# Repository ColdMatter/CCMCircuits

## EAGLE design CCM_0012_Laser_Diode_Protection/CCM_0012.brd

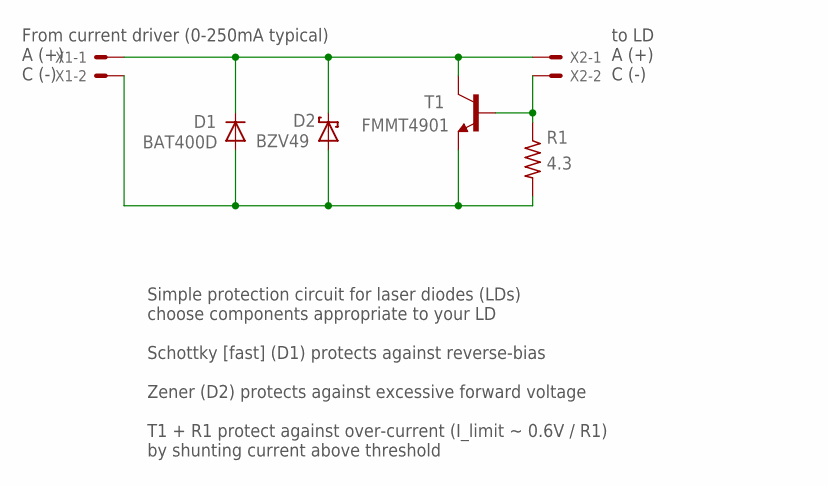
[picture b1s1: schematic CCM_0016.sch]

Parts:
D1: BAT400D; SOT23
D2: BZV49; SOT89
R1: 4.3; 2512
T1: FMMT4901; SOT23-BEC
X1, X2: 22-23-2021

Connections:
unnamed: R1.1, T1.B, X2.2
unnamed: D1.1 (A), D2.1 (A), D2.3 (A), R1.2, T1.E, X1.2
unnamed: D1.3 (C), D2.2 (C), D2.2@1 (C), T1.C, X1.1, X2.1

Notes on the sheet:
From current driver (0-250mA typical) A (+) C (-)
to LD A (+) C (-)
Simple protection circuit for laser diodes (LDs) choose components appropriate to your LD Schottky [fast] (D1) protects against reverse-bias Zener (D2) protects against excessive forward voltage T1 + R1 protect against over-current (I_limit ~ 0.6V / R1) by shunting current above threshold

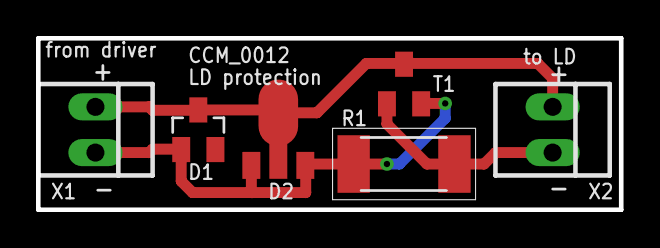
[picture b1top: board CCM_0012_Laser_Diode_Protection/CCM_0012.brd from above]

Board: 2 copper layers, 32.4 x 9.5 mm, 6 parts (0 on the bottom side), 3 nets.

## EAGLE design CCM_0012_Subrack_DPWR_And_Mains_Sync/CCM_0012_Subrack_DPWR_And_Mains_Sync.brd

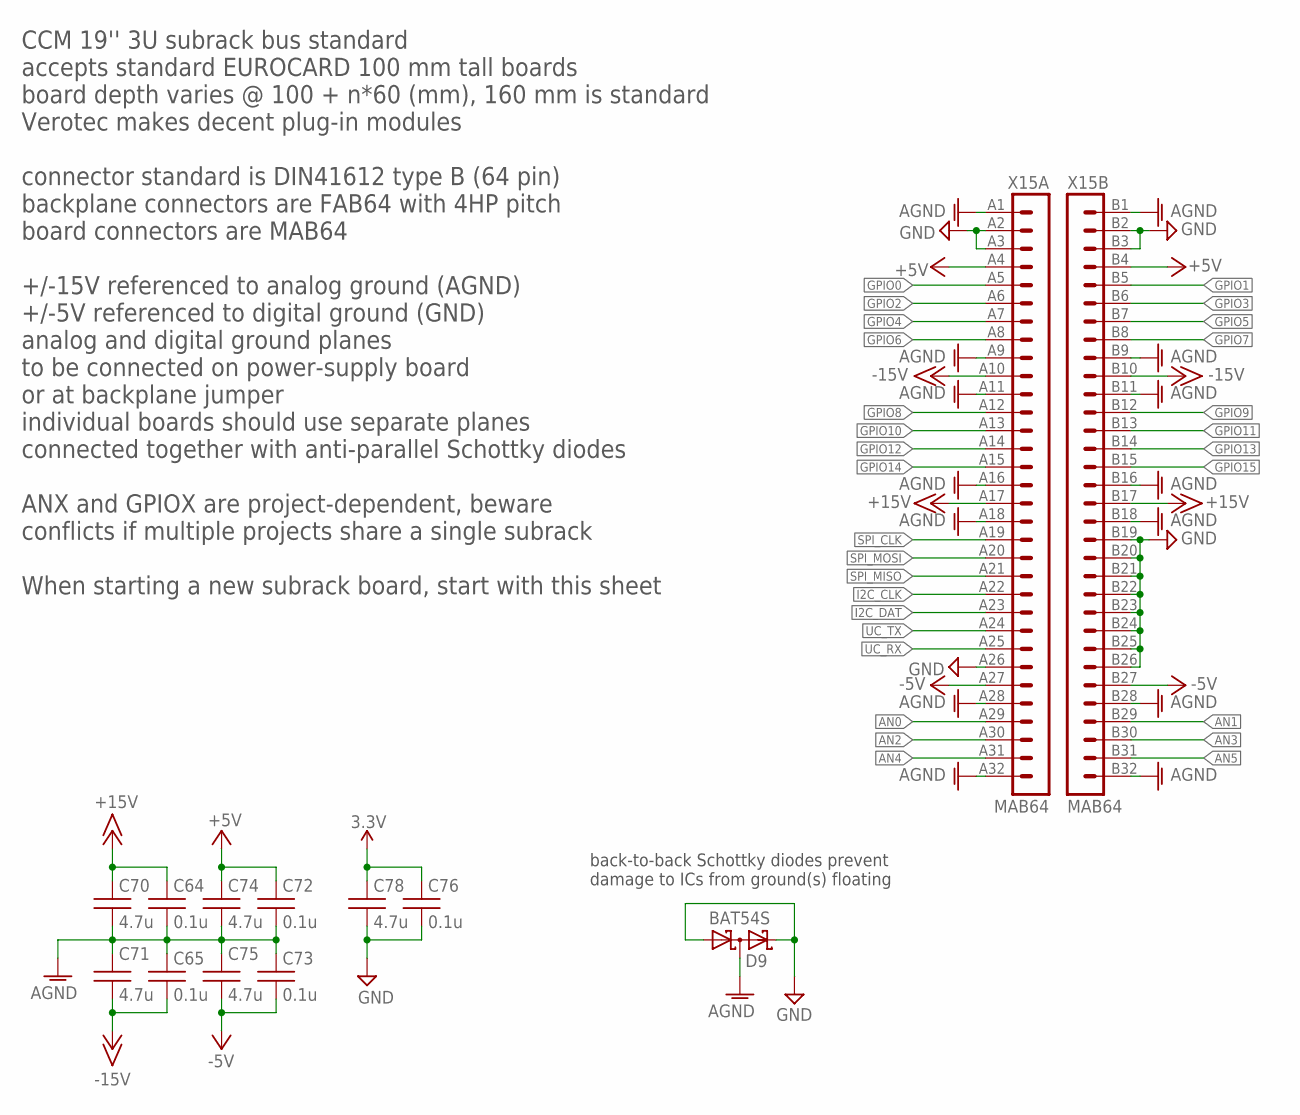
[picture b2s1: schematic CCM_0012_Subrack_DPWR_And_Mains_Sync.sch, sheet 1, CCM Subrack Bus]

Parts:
C64, C65, C72, C73, C76: 0.1u; 0603
C70, C71, C74, C75, C78: 4.7u; 0603
D9: BAT54S; SOT23
X15: MAB64

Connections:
3.3V: C76.1, C78.1
+5V: C72.1, C74.1, X15.A4 (4), X15.B4 (4)
+15V: C64.1, C70.1, X15.A17 (17), X15.B17 (17)
-5V: C73.2, C75.2, X15.A27 (27), X15.B27 (27)
-15V: C65.2, C71.2, X15.A10 (10), X15.B10 (10)
AGND: C64.2, C65.1, C70.2, C71.1, D9.3 (C1A2), X15.A1 (1), X15.A9 (9), X15.A11 (11), X15.A16 (16), X15.A18 (18), X15.A28 (28), X15.A32 (32), X15.B1 (1), X15.B9 (9), X15.B11 (11), X15.B16 (16), X15.B18 (18), X15.B28 (28), X15.B32 (32)
AGND1: C72.2, C73.1, C74.2, C75.1
AN0: X15.A29 (29)
AN1: X15.B29 (29)
AN2: X15.A30 (30)
AN3: X15.B30 (30)
AN4: X15.A31 (31)
AN5: X15.B31 (31)
GND: C76.2, C78.2, D9.1 (A1), D9.2 (C2), X15.A2 (2), X15.A3 (3), X15.A26 (26), X15.B2 (2), X15.B3 (3), X15.B19 (19), X15.B20 (20), X15.B21 (21), X15.B22 (22), X15.B23 (23), X15.B24 (24), X15.B25 (25), X15.B26 (26)
GPIO0: X15.A5 (5)
GPIO1: X15.B5 (5)
GPIO2: X15.A6 (6)
GPIO3: X15.B6 (6)
GPIO4: X15.A7 (7)
GPIO5: X15.B7 (7)
GPIO6: X15.A8 (8)
GPIO7: X15.B8 (8)
GPIO8: X15.A12 (12)
GPIO9: X15.B12 (12)
GPIO10: X15.A13 (13)
GPIO11: X15.B13 (13)
GPIO12: X15.A14 (14)
GPIO13: X15.B14 (14)
GPIO14: X15.A15 (15)
GPIO15: X15.B15 (15)
I2C_CLK: X15.A22 (22)
I2C_DAT: X15.A23 (23)
SPI_CLK: X15.A19 (19)
SPI_MISO: X15.A21 (21)
SPI_MOSI: X15.A20 (20)
UC_RX: X15.A25 (25)
UC_TX: X15.A24 (24)

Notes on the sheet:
back-to-back Schottky diodes prevent damage to ICs from ground(s) floating
CCM 19'' 3U subrack bus standard accepts standard EUROCARD 100 mm tall boards board depth varies @ 100 + n*60 (mm), 160 mm is standard Verotec makes decent plug-in modules connector standard is DIN41612 type B (64 pin) backplane connectors are FAB64 with 4HP pitch board connectors are MAB64 +/-15V 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

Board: 2 copper layers, 12 parts (0 on the bottom side), 8 nets, no tracks yet.

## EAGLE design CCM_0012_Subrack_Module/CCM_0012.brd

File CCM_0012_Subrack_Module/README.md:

# CCM_0012 Subrack Module

This is meant to be the starting point for any circuit/project that will be inserted into a subrack using the standarized CCM bus (see CCM_0011).  Standard board sizes are 160 x 100 mm.

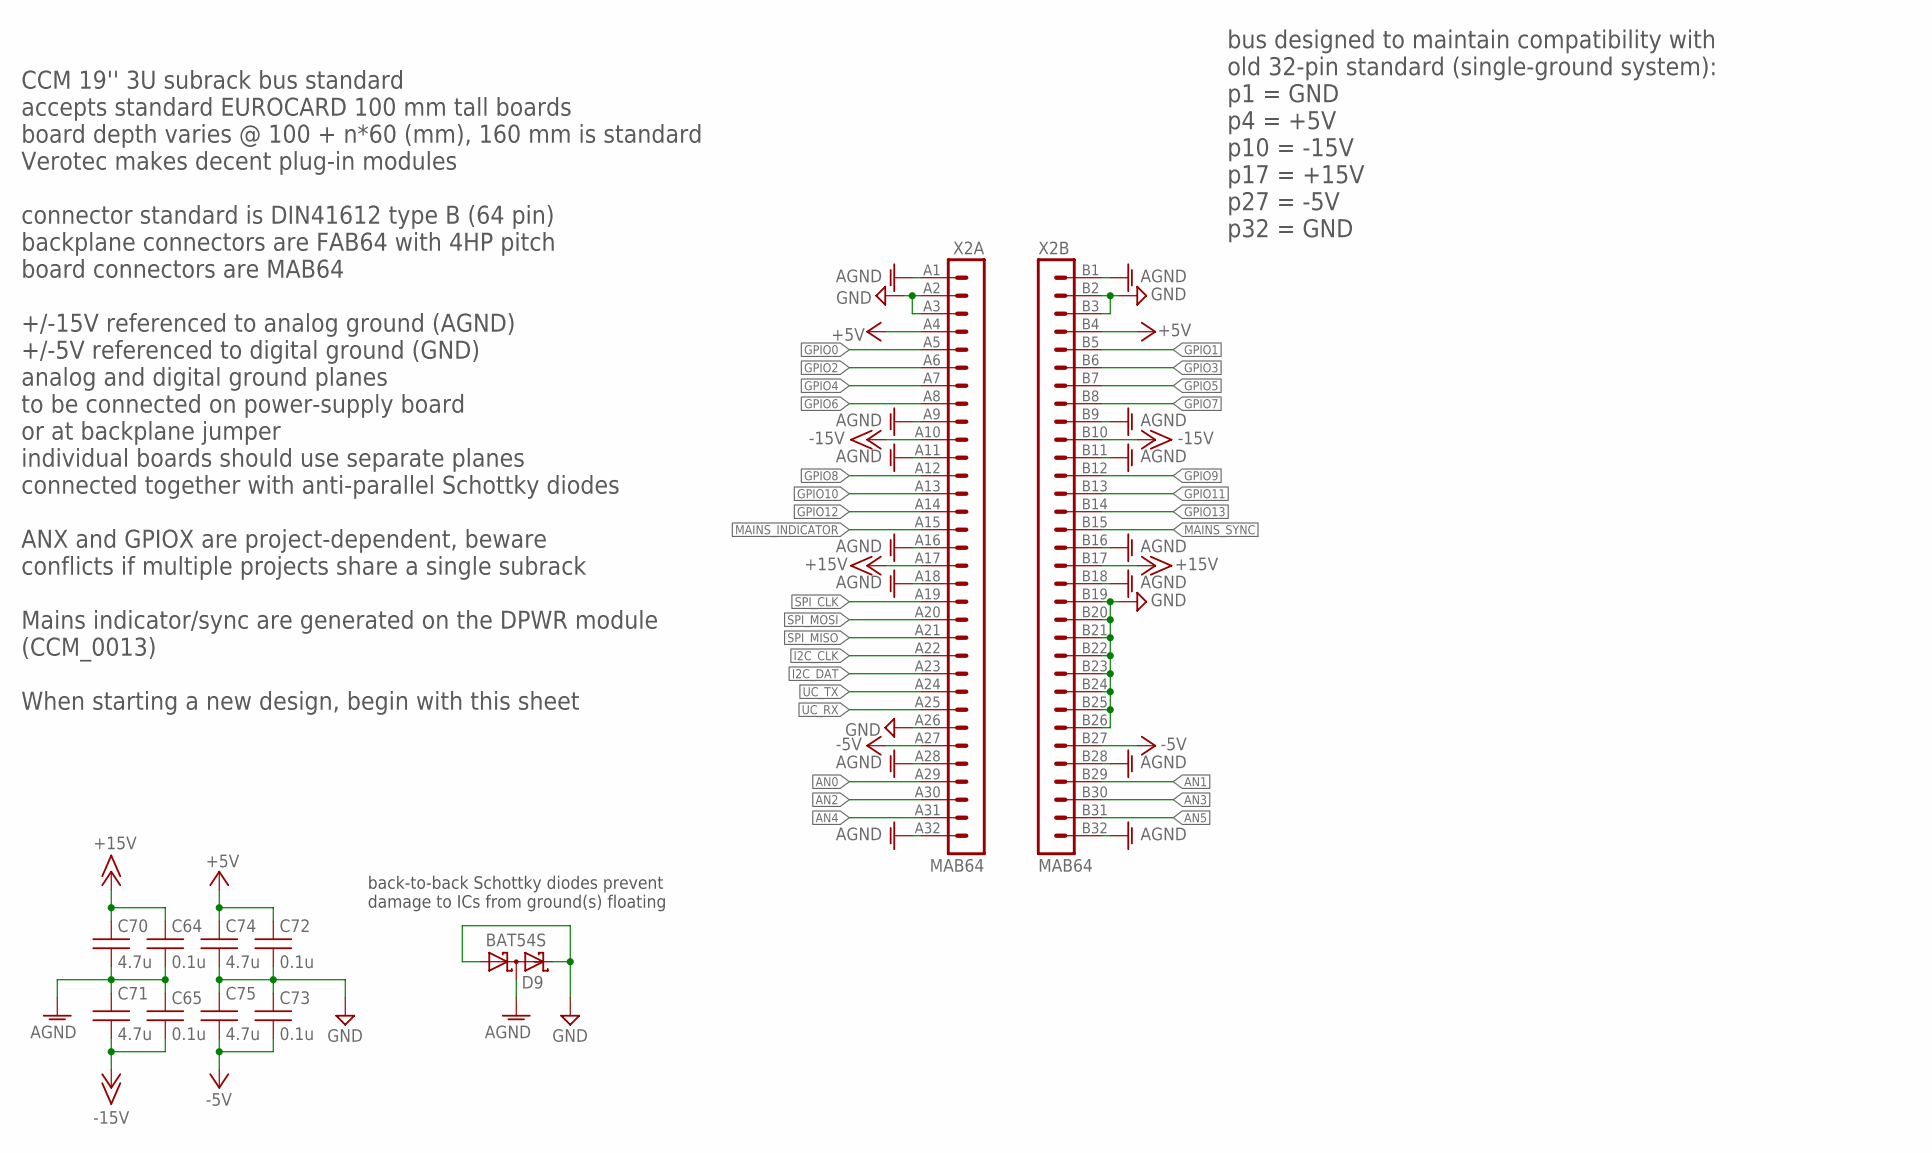
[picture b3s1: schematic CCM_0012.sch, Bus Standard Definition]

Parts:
C64, C65, C72, C73: 0.1u; 0603
C70, C71, C74, C75: 4.7u; 0603
D9: BAT54S; SOT23
X2: MAB64

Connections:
+5V: C72.1, C74.1, X2.A4 (4), X2.B4 (4)
+15V: C64.1, C70.1, X2.A17 (17), X2.B17 (17)
-5V: C73.2, C75.2, X2.A27 (27), X2.B27 (27)
-15V: C65.2, C71.2, X2.A10 (10), X2.B10 (10)
AGND: C64.2, C65.1, C70.2, C71.1, D9.3 (C1A2), X2.A1 (1), X2.A9 (9), X2.A11 (11), X2.A16 (16), X2.A18 (18), X2.A28 (28), X2.A32 (32), X2.B1 (1), X2.B9 (9), X2.B11 (11), X2.B16 (16), X2.B18 (18), X2.B28 (28), X2.B32 (32)
AN0: X2.A29 (29)
AN1: X2.B29 (29)
AN2: X2.A30 (30)
AN3: X2.B30 (30)
AN4: X2.A31 (31)
AN5: X2.B31 (31)
GND: C72.2, C73.1, C74.2, C75.1, D9.1 (A1), D9.2 (C2), X2.A2 (2), X2.A3 (3), X2.A26 (26), X2.B2 (2), X2.B3 (3), X2.B19 (19), X2.B20 (20), X2.B21 (21), X2.B22 (22), X2.B23 (23), X2.B24 (24), X2.B25 (25), X2.B26 (26)
GPIO0: X2.A5 (5)
GPIO1: X2.B5 (5)
GPIO2: X2.A6 (6)
GPIO3: X2.B6 (6)
GPIO4: X2.A7 (7)
GPIO5: X2.B7 (7)
GPIO6: X2.A8 (8)
GPIO7: X2.B8 (8)
GPIO8: X2.A12 (12)
GPIO9: X2.B12 (12)
GPIO10: X2.A13 (13)
GPIO11: X2.B13 (13)
GPIO12: X2.A14 (14)
GPIO13: X2.B14 (14)
I2C_CLK: X2.A22 (22)
I2C_DAT: X2.A23 (23)
MAINS_INDICATOR: X2.A15 (15)
MAINS_SYNC: X2.B15 (15)
SPI_CLK: X2.A19 (19)
SPI_MISO: X2.A21 (21)
SPI_MOSI: X2.A20 (20)
UC_RX: X2.A25 (25)
UC_TX: X2.A24 (24)

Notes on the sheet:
bus designed to maintain compatibility with old 32-pin standard (single-ground system): p1 = GND p4 = +5V p10 = -15V p17 = +15V p27 = -5V p32 = GND
CCM 19'' 3U subrack bus standard accepts standard EUROCARD 100 mm tall boards board depth varies @ 100 + n*60 (mm), 160 mm is standard Verotec makes decent plug-in modules connector standard is DIN41612 type B (64 pin) backplane connectors are FAB64 with 4HP pitch board connectors are MAB64 +/-15V 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
back-to-back Schottky diodes prevent damage to ICs from ground(s) floating

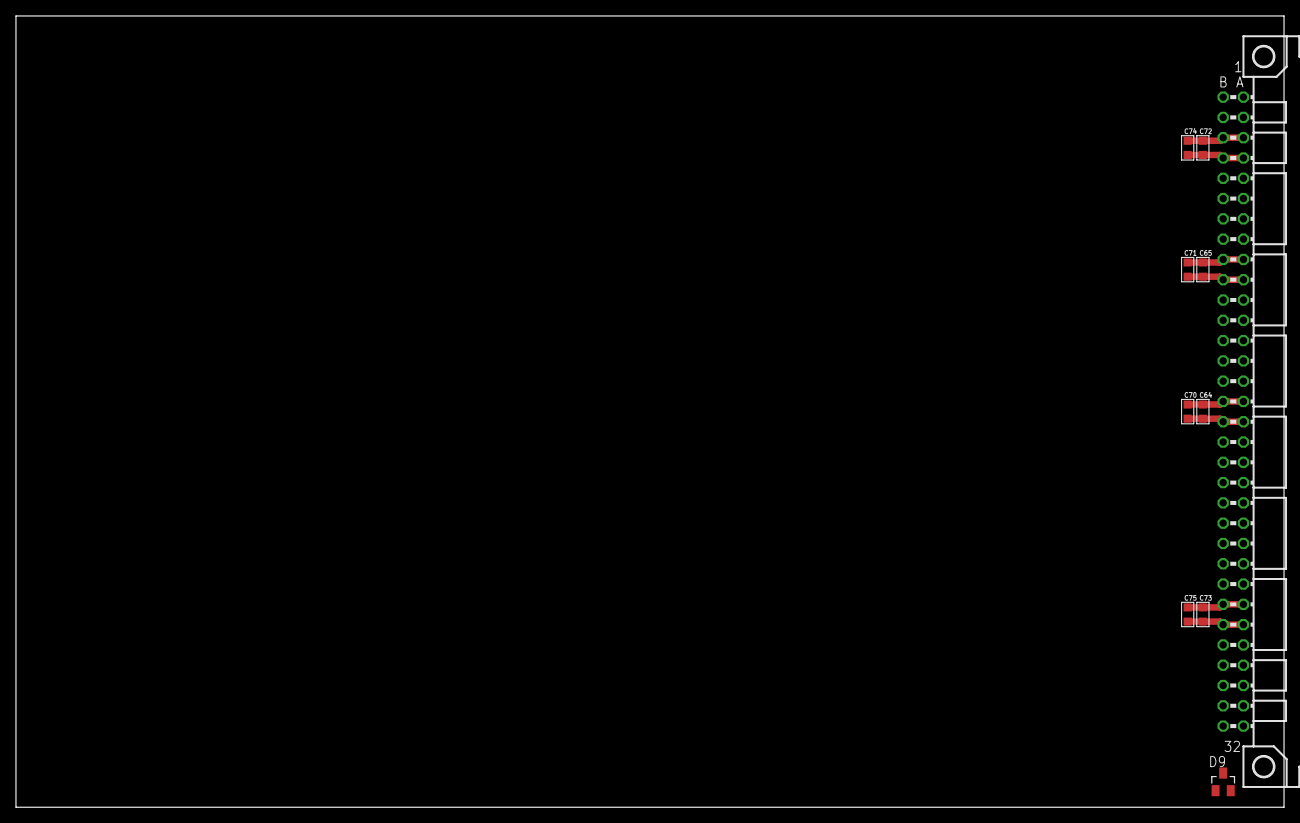
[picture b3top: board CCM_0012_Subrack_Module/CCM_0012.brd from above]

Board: 2 copper layers, 158.8 x 99.1 mm, 10 parts (0 on the bottom side), 6 nets.

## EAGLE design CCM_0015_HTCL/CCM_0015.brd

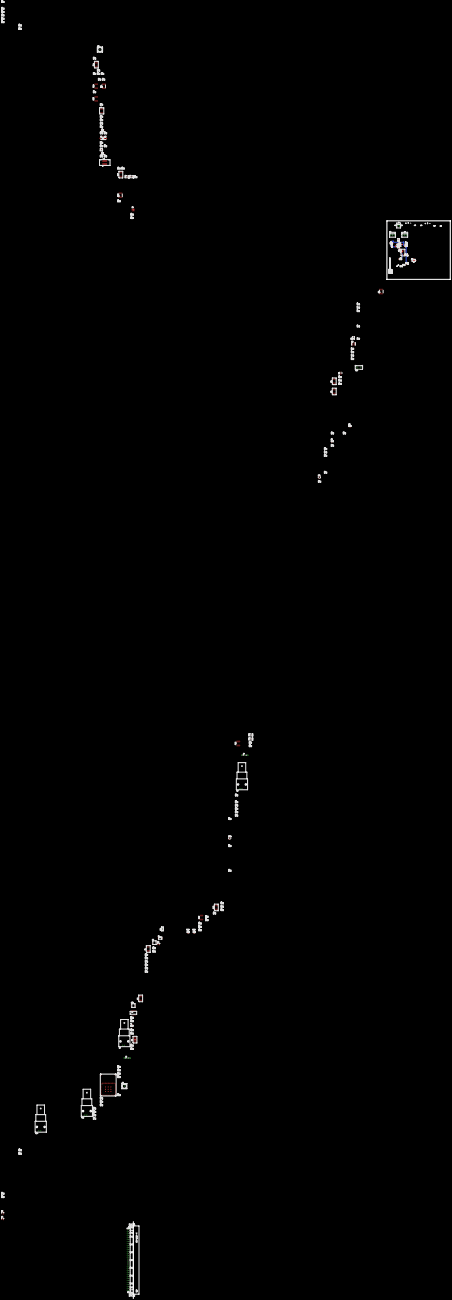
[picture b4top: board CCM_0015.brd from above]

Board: 2 copper layers, 178 parts (0 on the bottom side), 110 nets.

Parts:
C1, C2, C5, C6, C8, C9, C10, C11, C12, C13, C23, C24, C28, C29, C30, C38, C39, C41, C43, C46, C47, C48, C49, C50, C51, C52, C53, C54, C59, C60, C64, C65, C72, C73, C76: 0.1u; 0603
C3, C7: 10n; 0603
C4, C31, C32, C33: 100p; 0603
C19, C22, C44, C45: 10u; EIA3216
C26: 10p; 0603
C27, C34, C35: 1n; 0603
C36, C37, C40, C42: 1u; 0603
C55, C56, C57, C58, C70, C71, C74, C75, C78: 4.7u; 0603
C61: DNI; 0603
C62: 10nF; 0603
D0: RGB-LED-CLMVB-FKARGB; PLCC4-2MM-RGB
D2: BAV99; SOT23
D4, D5: LM4040-2.5V; SOT23
D7, D9: BAT54S; SOT23
IC1, IC8, IC13: AD8675; SO08
IC3, IC6, IC7: AD8675; SO8
IC4: TL331; DBV-R-PDSO-G5
IC5: AD9833; MSOP10
IC9, IC14: 741G3157DBVR; DBV_R-PDSO-G6
IC12: AD8672; SO8
IC15, IC18: 74AHC1G08DBV; SOT23-5
IC16: AD825_BR; SO8
IC17: LT1671; SO08
IC19, IC20: AD8041R; SO8
J1: SJ
J2, J3: 04C
JP0: JP1
Q1: SG-310SCN_10MHZ; ASF
R1, R2: 0; 0603
R3, R9, R39, R40, R43, R44, R46, R49, R59, R60, R61, R64, R65, R66: 1k; 0603
R4: 100k; 0603
R5, R6: 3.9k; 0603
R7, R11, R13, R14, R20, R21, R22, R37, R48, R50, R51, R55, R56, R58, R68, R69, R72, R73: 10k; 0603
R8, R45, R47: 1M; 0603
R10: 1.5k; 0603
R12: 30k; 0603
R15: 10k; 3386H
R35, R36, R38, R42, R57, R67, R70, R74: 100; 0603
R41: 5.1k; 0603
R52, R53: 40k; 0603
R54, R71: DNI; 0603
R62, R63: 27; 0603
S1, S2: TACTILE_SWITCH_SMD
T1: 3904SM; SOT23
TP1: TESTPOINT
U1: 741G74; TSSOP8
U2: AD8276; SO8
U4: AD5689; TSSOP16
U5: ADR4550; SO8
U6: AT25M01; SO-08
U7: AD7902; QSOP20
U8: ADP7104-2.5V; SO8-POWER
U9: PCA9502; QFN24-4X4
U10, U11: BUF634; SO8
U$2: AD5262; TSSOP16
U$3: P1; WM-N-BM-14
X2: 22-23-2021
X3, X5, X11, X14: 1-227161-0; AMP_227161
X4, X6: 22-23-2031
X7, X8: EZG-00-302
X9: SHF-105; SHF-105-01-X-D-SM
X10: USB-MICROB
X15: MAB64

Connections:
2.5V: C40.1, C41.1, U7.2, U7.7, U8.1, U8.2
3.3V: C2.1, C7.1, C9.1, C13.1, C76.1, C78.1, IC5.2, IC9.5, IC18.5, J2.3, Q1.4, R9.2, U1.2, U1.8, U4.5, U4.11, U7.15, U7.20, U9.1, U9.2, U9.3, U9.11, U9.22, U9.24, U$2.6, U$2.10, U$2.13
5V_REF: C36.1, C39.1, U4.1, U5.4, U7.1, U7.6
!CNV_RESET!: U1.6, U9.20
!DAC_RESET!: U4.15, U9.15
!EEPROM_SELECT!: U6.1, U$3.24
!P1_RESET: C12.1, R58.2, S1.1, S1.2, X9.10
!PDAG_CS!: U9.14, U$2.9
!SETUP: S2.1, S2.2, U$3.46
+3.3V: C48.1, C57.2, C58.2, C59.1, C60.1, D0.CA, R58.1, U6.3, U6.7, U6.8, U$3.2, U$3.3, U$3.5, U$3.26, U$3.27, U$3.38, X9.1
+5V: C42.1, C43.1, C72.1, C74.1, D2.1, D7.2, IC12.8, IC14.5, IC15.5, IC16.7, IC17.8, IC19.7, IC20.7, R21.1, R22.1, R50.2, U8.5, U8.8, U$2.5, X15.A4, X15.B4
+15V: C64.1, C70.1, X15.A17, X15.B17
-5V: C73.2, C75.2, IC12.4, IC16.4, IC17.4, J3.3, U$2.12, X15.A27, X15.B27
-15V: C65.2, C71.2, X15.A10, X15.B10
ABOVE_THRESHOLD: IC15.2, IC17.7, R47.2
AGND: C8.2, C10.1, C11.2, C19.C, C22.A, C23.2, C24.1, C27.2, C33.1, C34.2, C35.2, C36.2, C37.2, C38.2, C39.2, C40.2, C41.2, C42.2, C43.2, C44.C, C45.A, C46.2, C47.1, C62.2, C64.2, C65.1, C70.2, C71.1, D4.1, D5.2, D7.1, D9.3, IC1.3, IC3.3, IC5.4, IC5.9, IC6.3, IC8.3, IC12.3, IC13.3, IC14.2, IC16.3, IC17.2, IC19.4, IC20.4, J1.1, J2.1, J3.2, R37.2, R72.2, T1.2, U2.1, U4.4, U4.9, U4.10, U5.6, U7.4, U7.5, U7.9, U7.10, U8.3, U8.6, U8.PAD, U$2.11, X5.2, X7.2, X8.2, X11.2, X14.2, X15.A1, X15.A9, X15.A11, X15.A16, X15.A18, X15.A28, X15.A32, X15.B1, X15.B9, X15.B11, X15.B16, X15.B18, X15.B28, X15.B32
AGND1: C72.2, C73.1, C74.2, C75.1
CAVITY_DRIVE_RAW: C61.1, IC8.6, U11.3
CONVERT: U1.5, U7.11, U7.16, U9.21, U$3.41
D+: R62.2, X10.D+
D-: R63.2, X10.D-
DAC_RSTSEL: U4.16, U9.16
DERIVATIVE_ZERO_CROSSING: IC15.1, IC17.1, R45.1
GND: C1.1, C2.2, C5.2, C6.1, C9.2, C12.2, C13.2, C30.2, C48.2, C49.2, C50.2, C51.1, C52.1, C53.2, C54.1, C55.2, C56.1, C57.1, C58.1, C59.2, C60.2, C76.2, C78.2, D2.2, D9.1, D9.2, IC9.2, IC15.3, IC18.3, J1.2, Q1.2, R7.2, R48.1, S1.3, S1.4, S2.3, S2.4, TP1.P$1, U1.4, U6.4, U9.4, U9.9, U9.10, U9.17, U9.23, U9.EXP, U$3.1, U$3.4, U$3.6, U$3.13, U$3.15, U$3.25, U$3.28, U$3.37, U$3.39, U$3.59, U$3.65, U$3.66, U$3.67, U$3.68, U$3.69, U$3.70, U$3.71, U$3.72, U$3.73, X2.2, X9.3, X9.5, X9.9, X10.GND, X10.MT1, X10.MT2, X15.A2, X15.A3, X15.A26, X15.B2, X15.B3, X15.B19, X15.B20, X15.B21, X15.B22, X15.B23, X15.B24, X15.B25, X15.B26
I2C_CLK: R21.2, U$3.35, X15.A22
I2C_DAT: R22.2, U$3.36, X15.A23
LOCK: C35.1, R40.1, U2.3
N2: IC14.4, IC20.3, R42.2
unnamed: R64.1, U$3.48
unnamed: IC5.10, R2.2
unnamed: IC8.2, R11.1, R20.1, R68.2, R73.1
unnamed: IC4.3, R7.1, R8.2
unnamed: C1.2, IC5.3
unnamed: C3.1, R3.1
unnamed: C3.2, C4.2, IC3.2, R4.1
unnamed: C4.1, IC3.6, IC4.1, R4.2
unnamed: C10.2, D4.2, R14.2, R15.1
unnamed: IC7.3, R15.2
unnamed: R51.2, U2.5, U2.6
unnamed: IC6.2, R5.1, R6.1, R10.2
unnamed: C61.2, R68.1, R74.2, U11.6
unnamed: C11.1, D5.1, R13.1, R15.3
unnamed: R69.1, X11.1
unnamed: Q1.3, R1.2
unnamed: C7.2, IC5.1
unnamed: R65.1, U$3.49
unnamed: IC5.5, R1.1
unnamed: R66.1, U$3.50
unnamed: IC18.4, U1.1
unnamed: JP0.1, R10.1, R12.2
unnamed: IC12.7, R38.2, U$2.15
unnamed: J3.1, X3.2
unnamed: C26.1, D2.3, IC12.2, IC14.3, R35.1, U$2.2
unnamed: IC12.6, R37.1, U$2.16
unnamed: IC7.2, IC7.6, R6.2
unnamed: IC14.1, R38.1
unnamed: C27.1, IC12.5, R36.1
unnamed: C26.2, IC12.1, R36.2, U$2.3
unnamed: IC15.4, R41.1
unnamed: R39.2, U4.3
unnamed: IC18.1, R41.2, R48.2
unnamed: R35.2, X3.1
unnamed: J2.2, U2.2
unnamed: R49.2, T1.1
unnamed: C31.1, R42.1
unnamed: C32.2, IC16.6, R43.1, R44.2, R46.1
unnamed: R40.2, U4.7
unnamed: IC1.2, R51.1, R52.2, R53.1
unnamed: C31.2, C32.1, IC16.2, R43.2
unnamed: C33.2, IC17.3, R44.1, R45.2
unnamed: IC1.6, R52.1, R55.2
unnamed: IC17.5, R46.2, R47.1
unnamed: IC6.6, JP0.2, R12.1, R20.2
unnamed: IC19.2, IC19.6, R70.2
unnamed: R54.1, U10.1
unnamed: IC13.6, U10.3
unnamed: R56.1, R57.2, U10.6
unnamed: R53.2, X7.1
unnamed: R57.1, X5.1
unnamed: IC13.2, R55.1, R56.2
unnamed: R62.1, U$3.61
unnamed: D0.BLUE, R59.2
unnamed: D0.GREEN, R60.2
unnamed: D0.RED, R61.2
unnamed: R63.1, U$3.62
unnamed: IC20.2, IC20.6, R67.2
unnamed: R71.1, U11.1
unnamed: D7.3, IC19.3, R69.2, R72.1
unnamed: R73.2, X8.1
P1_SWDCLK: U$3.55, X9.4
P1_SWDIO: U$3.54, X9.2
PDA_EXT/!INT!: R49.1, U9.13
PDA_INTERNAL/!EXTERNAL!: IC14.6, R50.1, T1.3
PHOTODIODE: R67.1, U7.8
RAMP_CLK: IC4.4, R8.1, R9.1
RAMP_INDICATOR: C62.1, R70.1
RAMP_RAW: R74.1, X14.1
RGB_BLUE: R59.1, U$3.31
RGB_GREEN: R60.1, U$3.32
RGB_RED: R61.1, U$3.29
SPI_CLK: IC5.7, U4.12, U6.6, U7.13, U7.18, U9.8, U$2.7, U$3.22, X15.A19
SPI_MISO: U4.8, U6.2, U7.12, U7.17, U9.7, U$2.1, U$3.21, X15.A21
SPI_MOSI: IC5.6, U4.14, U6.5, U7.14, U7.19, U9.6, U$2.8, U$3.23, X15.A20
THRESHOLD: C34.1, IC17.6, R39.1
TWG_RAW: C8.1, R2.1, R3.2, R5.2
UC_RX: U$3.63, X15.A25
UC_TX: U$3.64, X15.A24
V+: C5.1, C19.A, C23.1, C37.1, C38.1, C44.A, C46.1, C49.1, C50.1, C53.1, C55.1, IC1.7, IC3.7, IC4.5, IC6.7, IC7.7, IC8.7, IC13.7, R13.2, U2.7, U5.2, U10.7, U11.7
V-: C6.2, C22.C, C24.2, C45.C, C47.2, C51.2, C52.2, C54.2, C56.2, IC1.4, IC3.4, IC4.2, IC6.4, IC7.4, IC8.4, IC13.4, R14.1, R54.2, R71.2, U2.4, U10.4, U11.4
ZDCAT_ENABLE: IC18.2, U$3.40

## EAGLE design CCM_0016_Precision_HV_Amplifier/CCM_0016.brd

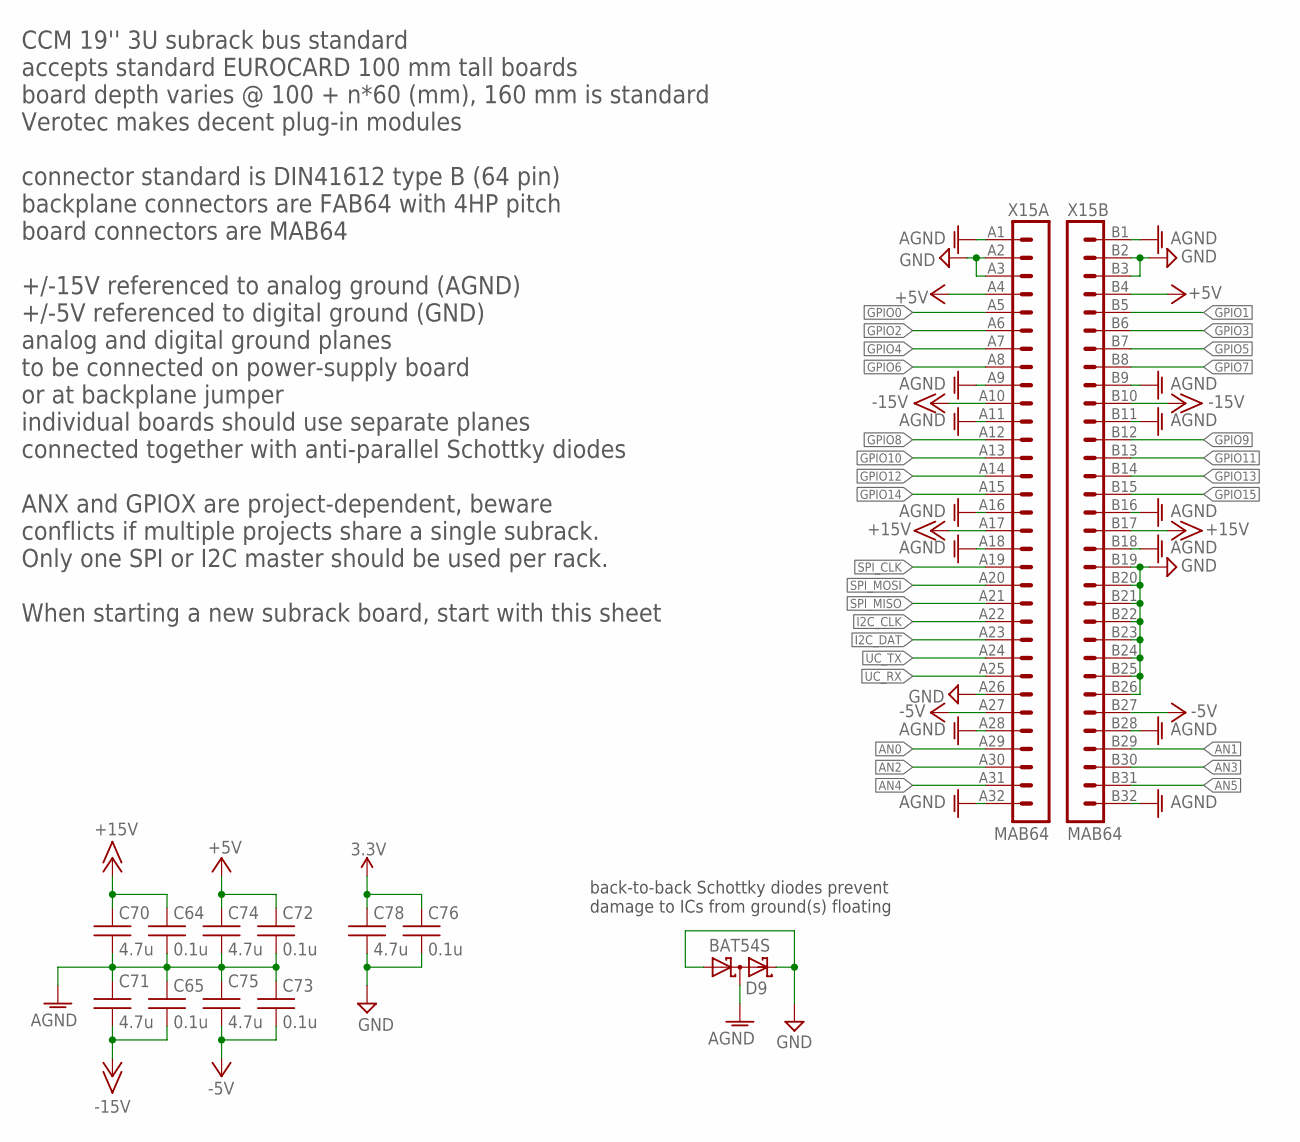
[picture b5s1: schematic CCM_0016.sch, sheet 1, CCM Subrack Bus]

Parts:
C64, C65, C72, C73, C76: 0.1u; 0603
C70, C71, C74, C75, C78: 4.7u; 0603
D9: BAT54S; SOT23
X15: MAB64

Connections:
3.3V: C76.1, C78.1
+5V: C72.1, C74.1, X15.A4 (4), X15.B4 (4)
+15V: C64.1, C70.1, X15.A17 (17), X15.B17 (17); also elsewhere on the board
-5V: C73.2, C75.2, X15.A27 (27), X15.B27 (27)
-15V: C65.2, C71.2, X15.A10 (10), X15.B10 (10); also elsewhere on the board
AGND: C64.2, C65.1, C70.2, C71.1, D9.3 (C1A2), X15.A1 (1), X15.A9 (9), X15.A11 (11), X15.A16 (16), X15.A18 (18), X15.A28 (28), X15.A32 (32), X15.B1 (1), X15.B9 (9), X15.B11 (11), X15.B16 (16), X15.B18 (18), X15.B28 (28), X15.B32 (32); also elsewhere on the board
AGND1: C72.2, C73.1, C74.2, C75.1
AN0: X15.A29 (29)
AN1: X15.B29 (29)
AN2: X15.A30 (30)
AN3: X15.B30 (30)
AN4: X15.A31 (31)
AN5: X15.B31 (31)
GND: C76.2, C78.2, D9.1 (A1), D9.2 (C2), X15.A2 (2), X15.A3 (3), X15.A26 (26), X15.B2 (2), X15.B3 (3), X15.B19 (19), X15.B20 (20), X15.B21 (21), X15.B22 (22), X15.B23 (23), X15.B24 (24), X15.B25 (25), X15.B26 (26)
GPIO0: X15.A5 (5)
GPIO1: X15.B5 (5)
GPIO2: X15.A6 (6)
GPIO3: X15.B6 (6)
GPIO4: X15.A7 (7)
GPIO5: X15.B7 (7)
GPIO6: X15.A8 (8)
GPIO7: X15.B8 (8)
GPIO8: X15.A12 (12)
GPIO9: X15.B12 (12)
GPIO10: X15.A13 (13)
GPIO11: X15.B13 (13)
GPIO12: X15.A14 (14)
GPIO13: X15.B14 (14)
GPIO14: X15.A15 (15)
GPIO15: X15.B15 (15)
I2C_CLK: X15.A22 (22)
I2C_DAT: X15.A23 (23)
SPI_CLK: X15.A19 (19)
SPI_MISO: X15.A21 (21)
SPI_MOSI: X15.A20 (20)
UC_RX: X15.A25 (25)
UC_TX: X15.A24 (24)

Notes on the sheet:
back-to-back Schottky diodes prevent damage to ICs from ground(s) floating
CCM 19'' 3U subrack bus standard accepts standard EUROCARD 100 mm tall boards board depth varies @ 100 + n*60 (mm), 160 mm is standard Verotec makes decent plug-in modules connector standard is DIN41612 type B (64 pin) backplane connectors are FAB64 with 4HP pitch board connectors are MAB64 +/-15V 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

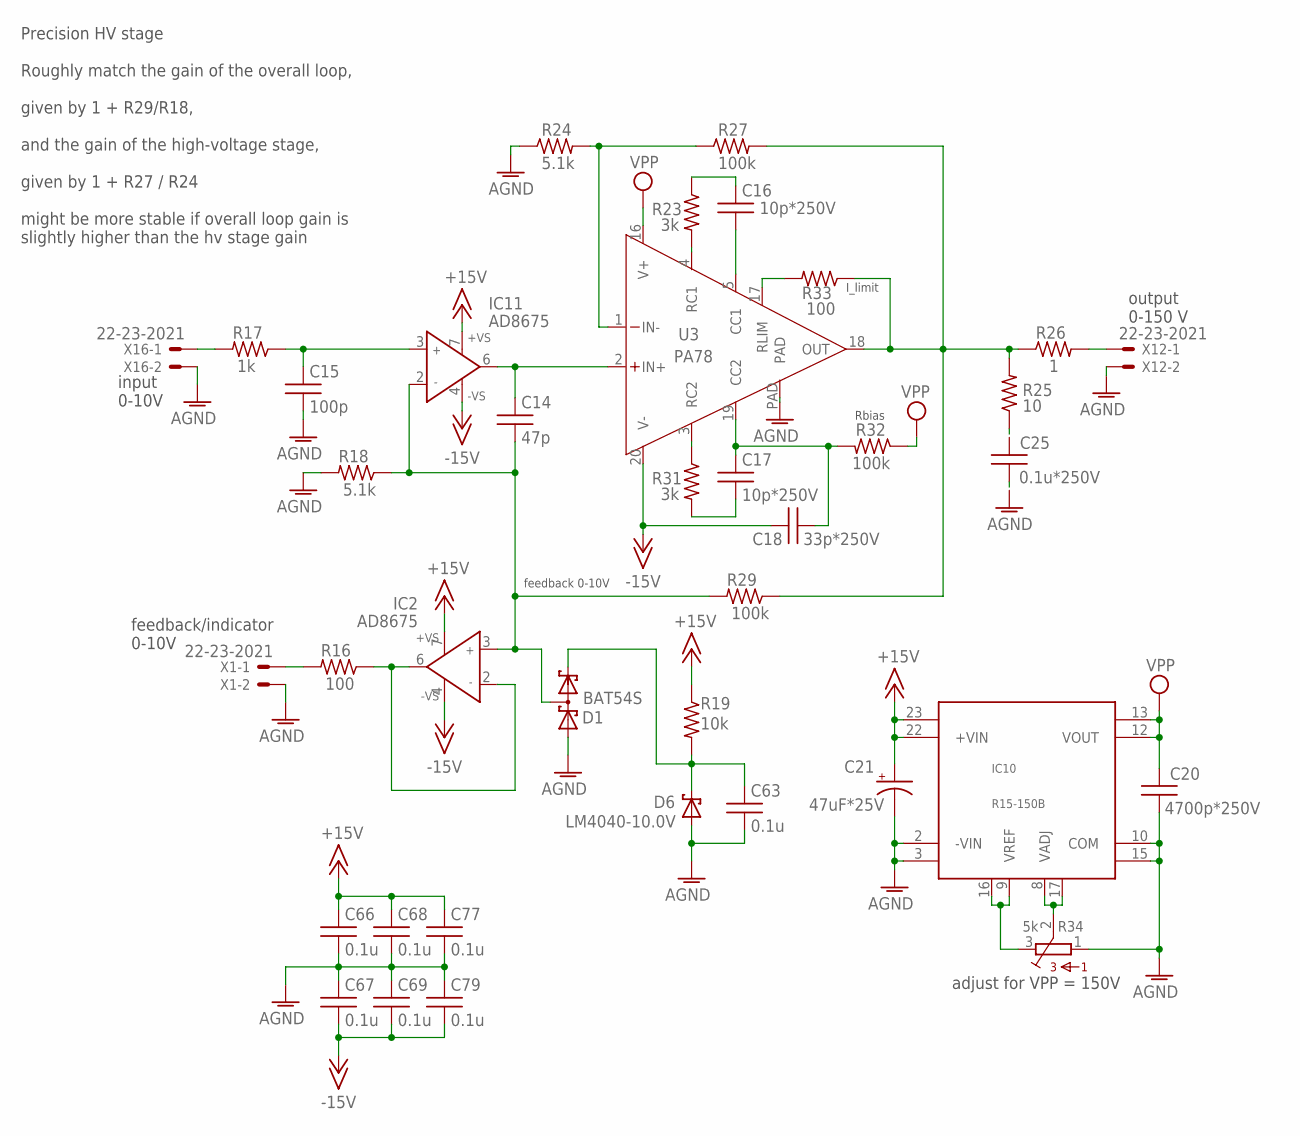
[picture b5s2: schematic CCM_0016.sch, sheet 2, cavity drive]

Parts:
C14: 47p; 0603
C15: 100p; 0603
C16, C17: 10p*250V; 0603
C18: 33p*250V; 0603
C20: 4700p*250V; 1210
C21: 47uF*25V; EIA7343
C25: 0.1u*250V; 1210
C63, C66, C67, C68, C69, C77, C79: 0.1u; 0603
D1: BAT54S; SOT23
D6: LM4040-10.0V; SOT23
IC2, IC11: AD8675; SO08
IC10: R15-150B; RXXDIP
R16, R33: 100; 0603
R17: 1k; 0603
R18, R24: 5.1k; 0603
R19: 10k; 0603
R23, R31: 3k; 0603
R25: 10; 2512
R26: 1; 2512
R27, R29, R32: 100k; 0603
R34: 5k; 3386H
U3: PA78; PSOP-20
X1, X12, X16: 22-23-2021

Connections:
+15V: C21.A (+), C66.1, C68.1, C77.1, IC2.7 (+VS), IC10.22 (+VIN), IC10.23 (VIN2+), IC11.7 (+VS), R19.1; also elsewhere on the board
-15V: C18.2, C67.2, C69.2, C79.2, IC2.4 (-VS), IC11.4 (-VS), U3.20 (V-); also elsewhere on the board
AGND: C15.2, C20.2, C21.C (-), C25.2, C63.2, C66.2, C67.1, C68.2, C69.1, C77.2, C79.1, D1.1 (A1), D6.2 (A), IC10.2 (-VIN), IC10.3 (VIN2-), IC10.10 (COM), IC10.15 (COM2), R18.2, R24.1, R34.1, U3.PAD, X12.2, X16.2; also elsewhere on the board
CAVITY_DRIVE_RAW: C14.1, IC11.6 (OUT), U3.2 (IN+)
unnamed: IC2.2 (IN-), IC2.6 (OUT), R16.1
unnamed: R17.2, X16.1
unnamed: C63.1, D1.2 (C2), D6.1 (C), R19.2
unnamed: C14.2, D1.3 (C1A2), IC2.3 (IN+), IC11.2 (IN-), R18.1, R29.2
unnamed: C15.1, IC11.3 (IN+), R17.1
unnamed: R26.2, X12.1
unnamed: C16.1, R23.1
unnamed: C25.1, R25.1
unnamed: R33.2, U3.17 (RLIM)
unnamed: R25.2, R26.1, R27.2, R29.1, R33.1, U3.18 (OUT)
unnamed: R23.2, U3.4 (RC1)
unnamed: R24.2, R27.1, U3.1 (IN-)
unnamed: C16.2, U3.5 (CC1)
unnamed: R31.1, U3.3 (RC2)
unnamed: C17.1, C18.1, R32.2, U3.19 (CC2)
unnamed: C17.2, R31.2
unnamed: IC10.9 (VREF), IC10.16 (VREF2), R34.3
unnamed: IC10.8 (VADJ), IC10.17 (VADJ2), R34.2
VOUT2: C20.1, IC10.12 (VOUT), IC10.13 (VOUT2)
VPP: R32.1, U3.16 (V+)

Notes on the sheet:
feedback 0-10V
Precision HV stage Roughly match the gain of the overall loop, given by 1 + R29/R18, and the gain of the high-voltage stage, given by 1 + R27 / R24 might be more stable if overall loop gain is slightly higher than the hv stage gain
output 0-150 V
Rbias
I_limit
adjust for VPP = 150V
input 0-10V
feedback/indicator 0-10V

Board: 2 copper layers, 50 parts (0 on the bottom side), 29 nets, no tracks yet.

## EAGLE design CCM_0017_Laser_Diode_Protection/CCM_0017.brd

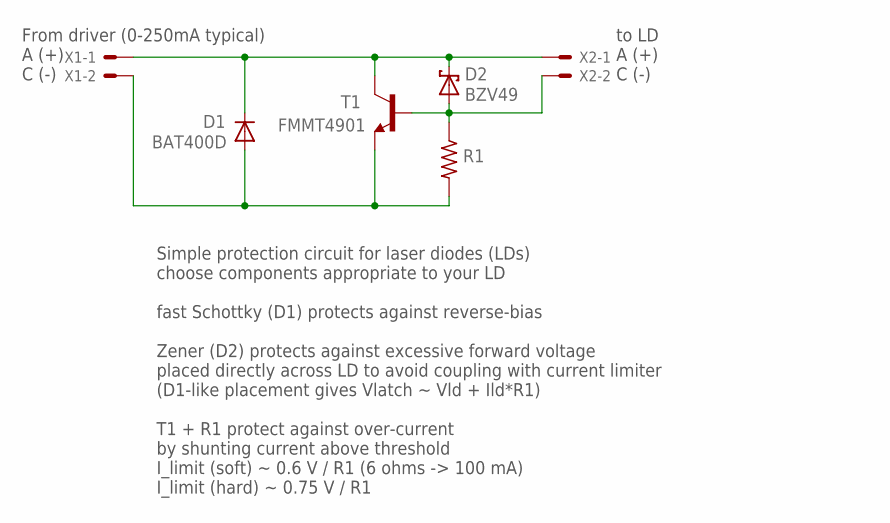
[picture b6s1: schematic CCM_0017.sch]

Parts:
D1: BAT400D; SOT23
D2: BZV49; SOT89
R1: 4.3; 1210
T1: FMMT4901; SOT23-BEC
X1, X2: 22-23-2021

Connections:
unnamed: D2.1 (A), D2.3 (A), R1.1, T1.B, X2.2
unnamed: D1.1 (A), R1.2, T1.E, X1.2
unnamed: D1.3 (C), D2.2 (C), D2.2@1 (C), T1.C, X1.1, X2.1

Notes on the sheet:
From driver (0-250mA typical) A (+) C (-)
to LD A (+) C (-)
Simple protection circuit for laser diodes (LDs) choose components appropriate to your LD fast Schottky (D1) protects against reverse-bias Zener (D2) protects against excessive forward voltage placed directly across LD to avoid coupling with current limiter (D1-like placement gives Vlatch ~ Vld + I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

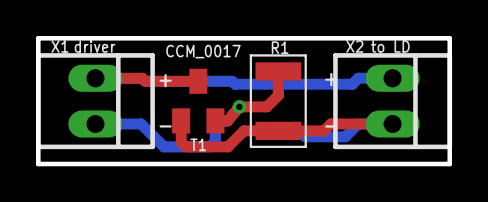
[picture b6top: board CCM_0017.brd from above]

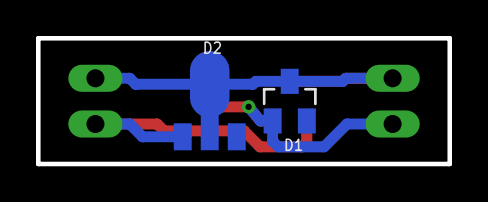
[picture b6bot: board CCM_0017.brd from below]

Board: 2 copper layers, 22.9 x 7.0 mm, 6 parts (2 on the bottom side), 3 nets.

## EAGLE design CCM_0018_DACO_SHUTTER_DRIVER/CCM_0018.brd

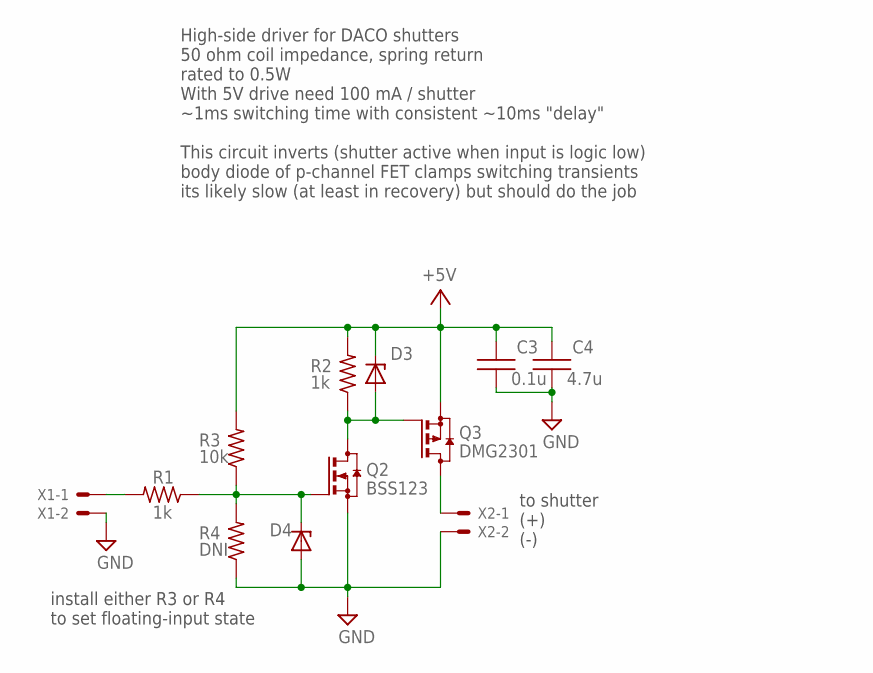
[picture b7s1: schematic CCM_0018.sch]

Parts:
C3: 0.1u; 0603
C4: 4.7u; 0603
D3, D4: ZENER-DIODESOT23; SOT23
Q2: BSS123; SOT23
Q3: DMG2301; SOT23
R1, R2: 1k; 0603
R3: 10k; 0603
R4: DNI; 0603
X1, X2: 22-23-2021

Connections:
+5V: C3.1, C4.1, D3.3 (C), Q3.2 (S), R2.2, R3.2
GND: C3.2, C4.2, D4.1 (A), Q2.2 (S), R4.1, X1.2, X2.2
unnamed: D4.3 (C), Q2.1 (G), R1.1, R3.1, R4.2
unnamed: D3.1 (A), Q2.3 (D), Q3.1 (G), R2.1
unnamed: Q3.3 (D), X2.1
unnamed: R1.2, X1.1

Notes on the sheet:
to shutter (+) (-)
High-side driver for DACO shutters 50 ohm coil impedance, spring return rated to 0.5W With 5V drive need 100 mA / shutter ~1ms switching time with consistent ~10ms "delay" This circuit inverts (shutter active when input is logic low) body diode of p-channel FET clamps switching transients its likel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
install either R3 or R4 to set floating-input state

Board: 2 copper layers, 12 parts (0 on the bottom side), 6 nets, no tracks yet.
